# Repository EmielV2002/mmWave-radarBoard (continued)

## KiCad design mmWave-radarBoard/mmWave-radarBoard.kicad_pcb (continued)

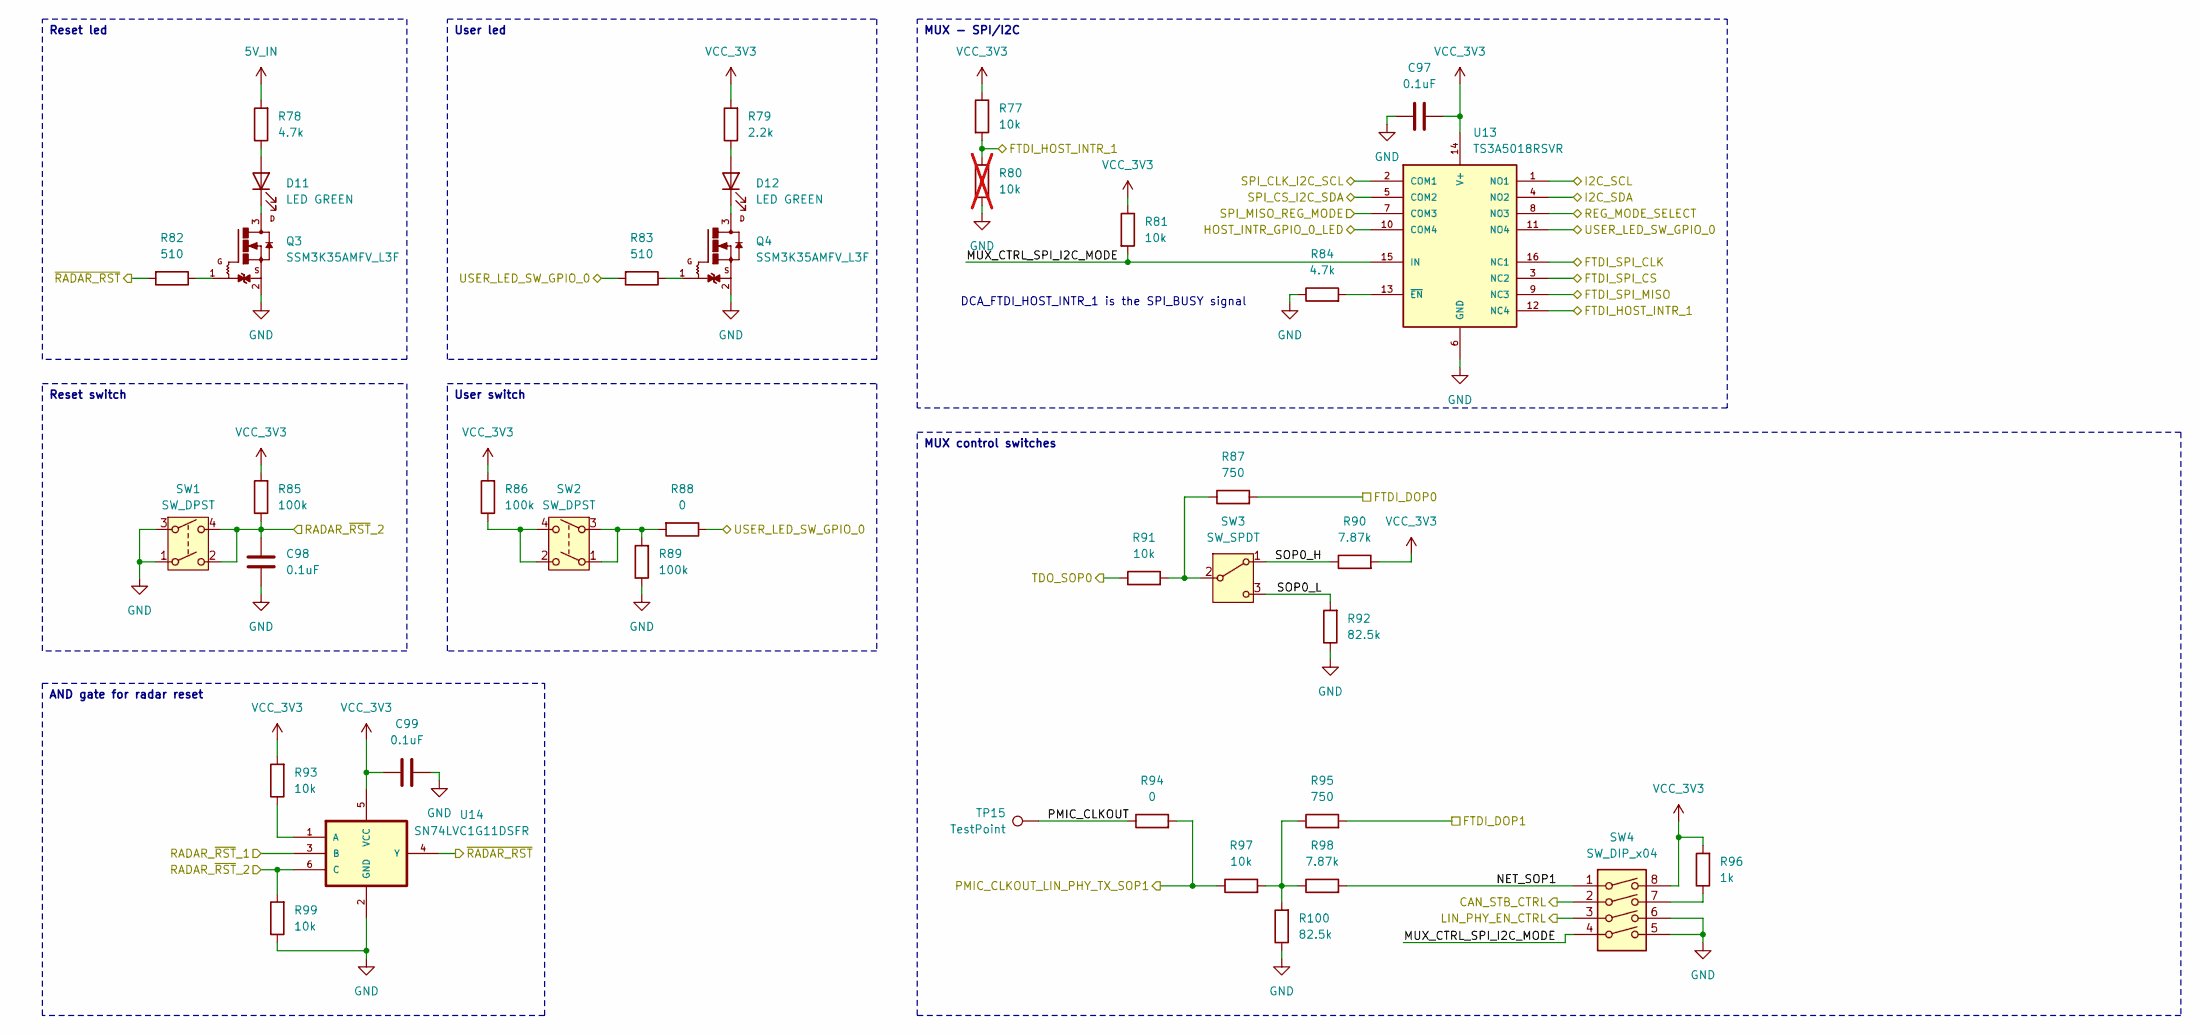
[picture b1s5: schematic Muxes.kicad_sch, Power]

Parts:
C97, C99: 0.1uF; C_0402_1005Metric
C98: 0.1uF; C_0603_1608Metric
D11, D12: LED GREEN; LED_0603_1608Metric
Q3, Q4: SSM3K35AMFV_L3F; VESM_TOS-M; MANUFACTURER_PART_NUMBER SSM3K35AMFV,L3F
R77, R81, R93, R99: 10k; R_0402_1005Metric
R78: 4.7k; R_0603_1608Metric
R79: 2.2k; R_0603_1608Metric
R80: 10k; R_0402_1005Metric; not fitted
R82, R83: 510; R_0402_1005Metric
R84: 4.7k; R_0402_1005Metric
R85, R86, R89: 100k; R_0603_1608Metric
R87, R95: 750; R_0603_1608Metric
R88, R94: 0; R_0603_1608Metric
R90, R98: 7.87k; R_0603_1608Metric
R91, R97: 10k; R_0603_1608Metric
R92, R100: 82.5k; R_0603_1608Metric
R96: 1k; R_0603_1608Metric
SW1, SW2: SW_DPST; SW_SPST_PTS810
SW3: SW_SPDT; Nidec_Copal_CAS-120A
SW4: SW_DIP_x04; SW_DIP_SPSTx04_Slide_6.7x11.72mm_W8.61mm_P2.54mm_LowProfile
TP15: TestPoint; TestPoint_Pad_D1.0mm
U13: TS3A5018RSVR; QFN40P260X180X55-16N; PARTREV 4220314/C 02/2020
U14: SN74LVC1G11DSFR; SON35P100X100X40-6N

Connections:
5V_IN: R78.2; also elsewhere on the board
/CAN_STB_CTRL: SW4.2; also elsewhere on the board
/FTDI_HOST_INT_1: R77.2, R80.1, U13.12 (NC4); also elsewhere on the board
/FTDI_SOP0: R87.2; also elsewhere on the board
/FTDI_SOP1: R95.2; also elsewhere on the board
/FTDI_SPI_CLK: U13.16 (NC1); also elsewhere on the board
/FTDI_SPI_CS: U13.3 (NC2); also elsewhere on the board
/FTDI_SPI_MISO: U13.9 (NC3); also elsewhere on the board
/HOST_INTR_GPIO_0_LED: U13.10 (COM4); also elsewhere on the board
/I2C_SCL: U13.1 (NO1); also elsewhere on the board
/I2C_SDA: U13.4 (NO2); also elsewhere on the board
/LIN_PHY_EN_CTRL: SW4.3; also elsewhere on the board
/Muxes/MUX_CTRL_SPI_I2C_MODE: R81.2, SW4.4, U13.15 (IN)
/Muxes/NET_SOP1: R98.2, SW4.1
/Muxes/PMIC_CLKOUT: R94.1, TP15.1
/Muxes/SOP0_H: R90.1, SW3.1 (A)
/Muxes/SOP0_L: R92.2, SW3.3 (C)
/PMIC_CLKOUT_LIN_PHY_TX_SOP1: R94.2, R97.1; also elsewhere on the board
/RADAR_~RST: R82.2, U14.4 (Y); also elsewhere on the board
/RADAR_~RST_1: U14.3 (B); also elsewhere on the board
/RADAR_~RST_2: C98.2, R85.1, R99.2, SW1.2, SW1.4, U14.6 (C); also elsewhere on the board
/REG_MODE_SELECT: U13.8 (NO3); also elsewhere on the board
/SPI_CLK_I2C_SCL: U13.2 (COM1); also elsewhere on the board
/SPI_CS_I2C_SDA: U13.5 (COM2); also elsewhere on the board
/SPI_MISO_REG_MODE: U13.7 (COM3); also elsewhere on the board
/TDO_SOP0: R91.1; also elsewhere on the board
/USER_LED_SW_GPIO_0: R83.2, R88.1, U13.11 (NO4); also elsewhere on the board
GND: C97.1, C98.1, C99.2, Q3.2, Q4.2, R80.2, R84.1, R89.1, R92.1, R99.1, R100.1, SW1.1, SW1.3, SW4.5, SW4.6, U13.6 (GND), U14.2 (GND); also elsewhere on the board
unnamed: D11.2 (A), R78.1
unnamed: D11.1 (K), Q3.3
unnamed: D12.2 (A), R79.1
unnamed: D12.1 (K), Q4.3
unnamed: Q3.1, R82.1
unnamed: Q4.1, R83.1
unnamed: R86.1, SW2.2, SW2.4
unnamed: R88.2, R89.2, SW2.1, SW2.3
unnamed: R96.1, SW4.7
unnamed: R95.1, R97.2, R98.1, R100.2
unnamed: R87.1, R91.2, SW3.2 (B)
unnamed: R84.2, U13.13 (~EN)
unnamed: R93.1, U14.1 (A)
VCC_3V3: C97.2, C99.1, R77.1, R79.2, R81.1, R85.2, R86.2, R90.2, R93.2, R96.2, SW4.8, U13.14 (V+), U14.5 (VCC); also elsewhere on the board

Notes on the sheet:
DCA_FTDI_HOST_INTR_1 is the SPI_BUSY signal
AND gate for radar reset
Reset led
MUX - SPI/I2C
Reset switch
User led
MUX control switches
User switch

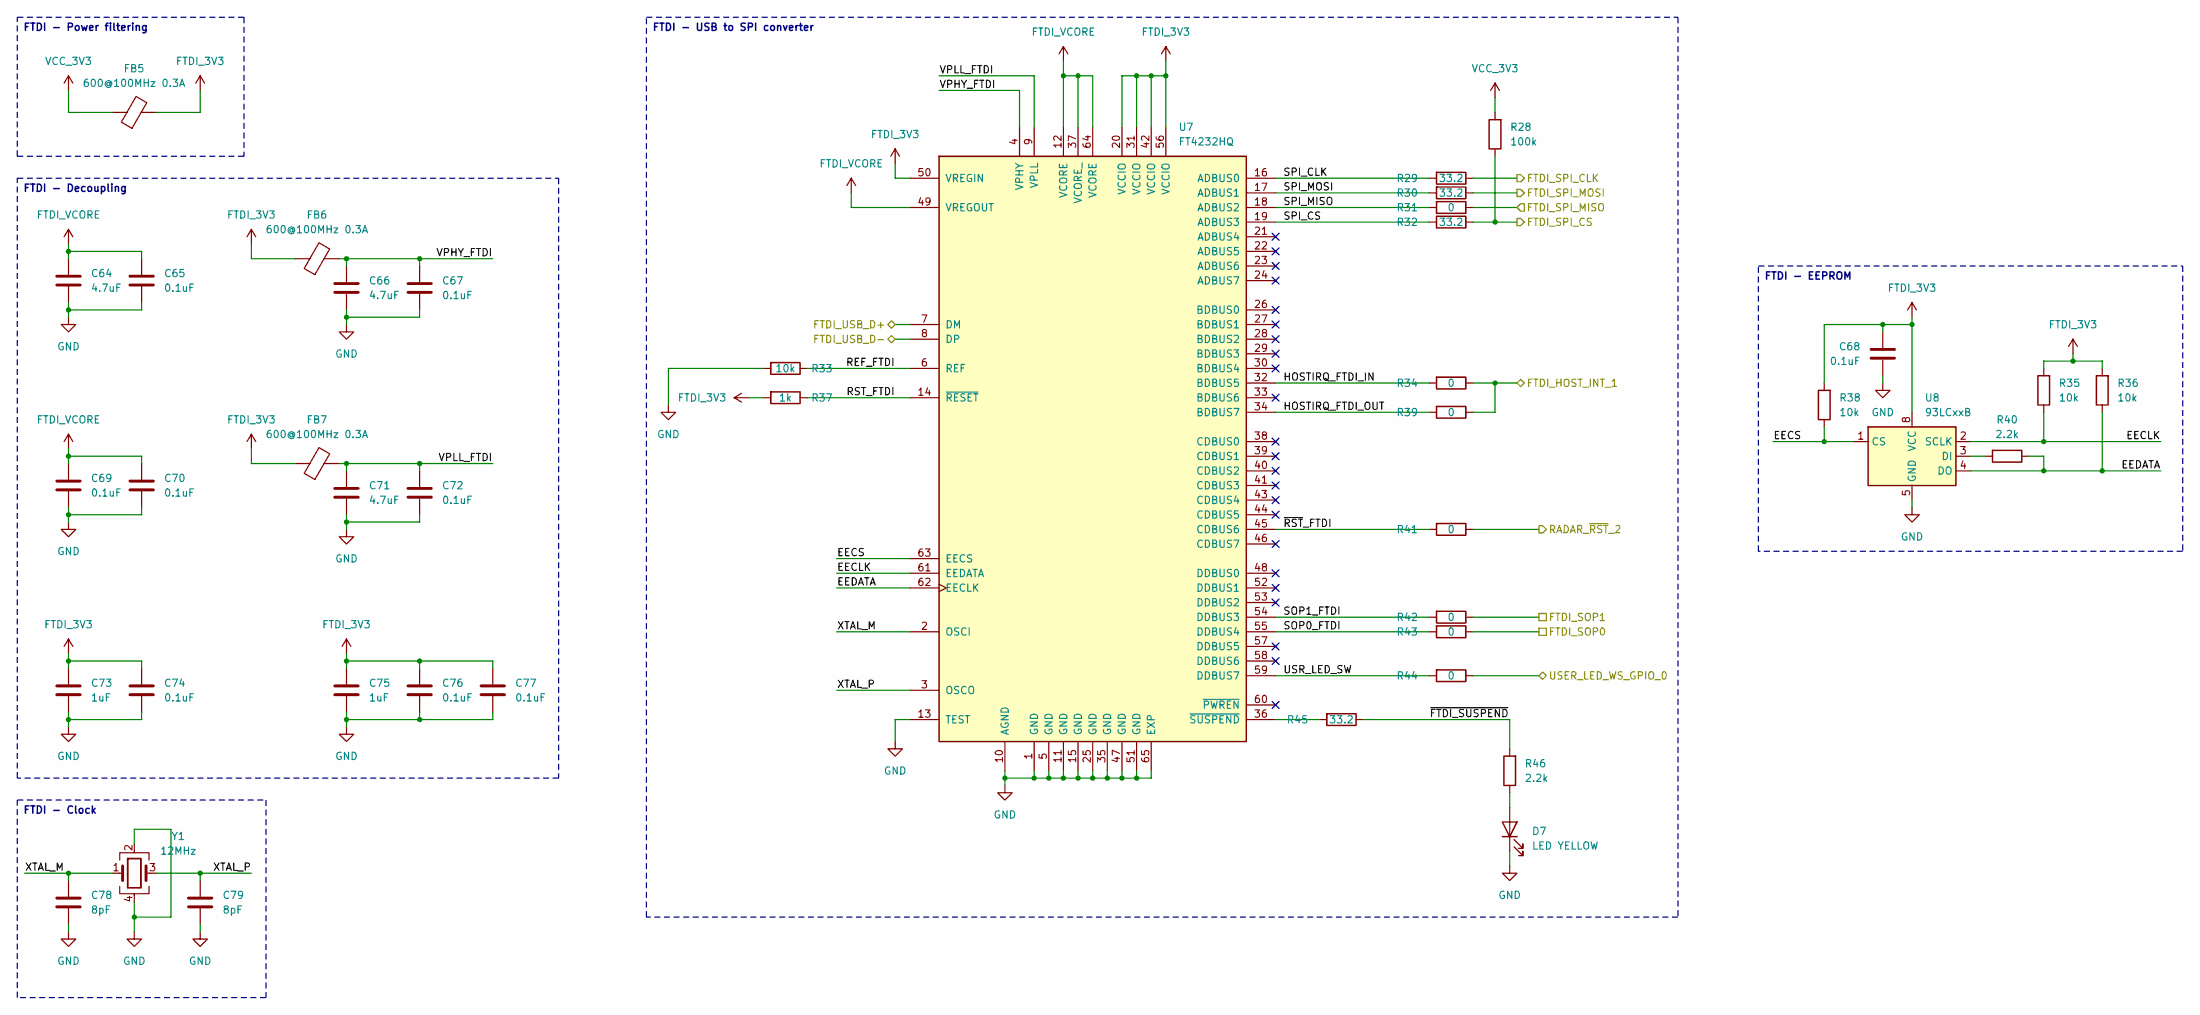
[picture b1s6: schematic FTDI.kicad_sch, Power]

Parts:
C64, C66, C71: 4.7uF; C_0402_1005Metric
C65, C67, C69, C70, C72, C74, C76, C77: 0.1uF; C_0402_1005Metric
C68: 0.1uF; C_0603_1608Metric
C73, C75: 1uF; C_0402_1005Metric
C78, C79: 8pF; C_0402_1005Metric
D7: LED YELLOW; LED_0603_1608Metric
FB5, FB6, FB7: 600@100MHz 0.3A; L_0603_1608Metric
R28: 100k; R_0402_1005Metric
R29, R30, R32, R45: 33.2; R_0402_1005Metric
R31, R34, R39, R41, R42, R43, R44: 0; R_0402_1005Metric
R33, R35, R36, R38: 10k; R_0402_1005Metric
R37: 1k; R_0402_1005Metric
R40: 2.2k; R_0402_1005Metric
R46: 2.2k; R_0603_1608Metric
U7: FT4232HQ; QFN50P900X900X105-65N; PARTREV 2.5
U8: 93LCxxB; SOIC-8_3.9x4.9mm_P1.27mm
Y1: 12MHz; Crystal_SMD_2016-4Pin_2.0x1.6mm

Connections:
/FTDI/EECLK: R35.1, U7.61 (EEDATA), U8.2 (SCLK)
/FTDI/EECS: R38.1, U7.63 (EECS), U8.1 (CS)
/FTDI/EEDATA: R36.1, R40.1, U7.62 (EECLK), U8.4 (DO)
/FTDI/HOSTIRQ_FTDI_IN: R34.2, U7.32 (BDBUS5)
/FTDI/HOSTIRQ_FTDI_OUT: R39.2, U7.34 (BDBUS7)
/FTDI/REF_FTDI: R33.1, U7.6 (REF)
/FTDI/RST_FTDI: R37.1, U7.14 (~RESET)
/FTDI/SOP0_FTDI: R43.2, U7.55 (DDBUS4)
/FTDI/SOP1_FTDI: R42.2, U7.54 (DDBUS3)
/FTDI/SPI_CLK: R29.2, U7.16 (ADBUS0)
/FTDI/SPI_CS: R32.2, U7.19 (ADBUS3)
/FTDI/SPI_MISO: R31.2, U7.18 (ADBUS2)
/FTDI/SPI_MOSI: R30.2, U7.17 (ADBUS1)
/FTDI/USR_LED_SW: R44.2, U7.59 (DDBUS7)
/FTDI/VPHY_FTDI: C66.1, C67.1, FB6.2, U7.4 (VPHY)
/FTDI/VPLL_FTDI: C71.1, C72.1, FB7.2, U7.9 (VPLL)
/FTDI/XTAL_M: C78.1, U7.2 (OSCI), Y1.1
/FTDI/XTAL_P: C79.1, U7.3 (OSCO), Y1.3
/FTDI/~FTDI_SUSPEND: R45.1, R46.2
/FTDI/~RST_FTDI: R41.2, U7.45 (CDBUS6)
/FTDI_HOST_INT_1: R34.1, R39.1; also elsewhere on the board
/FTDI_SOP0: R43.1; also elsewhere on the board
/FTDI_SOP1: R42.1; also elsewhere on the board
/FTDI_SPI_CLK: R29.1; also elsewhere on the board
/FTDI_SPI_CS: R28.1, R32.1; also elsewhere on the board
/FTDI_SPI_MISO: R30.1; also elsewhere on the board
/FTDI_SPI_MOSI: R31.1; also elsewhere on the board
/RADAR_~RST_2: R41.1; also elsewhere on the board
/USB_D+: U7.7 (DM); also elsewhere on the board
/USB_D-: U7.8 (DP); also elsewhere on the board
/USER_LED_SW_GPIO_0: R44.1; also elsewhere on the board
FTDI_3V3: C68.1, C73.1, C74.1, C75.1, C76.1, C77.1, FB5.2, FB6.1, FB7.1, R35.2, R36.2, R37.2, R38.2, U7.20 (VCCIO), U7.31 (VCCIO), U7.42 (VCCIO), U7.50 (VREGIN), U7.56 (VCCIO), U8.8 (VCC)
FTDI_VCORE: C64.1, C65.1, C69.1, C70.1, U7.12 (VCORE), U7.37 (VCORE_), U7.49 (VREGOUT), U7.64 (VCORE)
GND: C64.2, C65.2, C66.2, C67.2, C68.2, C69.2, C70.2, C71.2, C72.2, C73.2, C74.2, C75.2, C76.2, C77.2, C78.2, C79.2, D7.1 (K), R33.2, U7.1 (GND), U7.5 (GND), U7.10 (AGND), U7.11 (GND), U7.13 (TEST), U7.15 (GND), U7.25 (GND), U7.35 (GND), U7.47 (GND), U7.51 (GND), U7.65 (EXP), U8.5 (GND), Y1.2, Y1.4; also elsewhere on the board
unnamed: D7.2 (A), R46.1
unnamed: R45.2, U7.36 (~SUSPEND)
unnamed: R40.2, U8.3 (DI)
VCC_3V3: FB5.1, R28.2; also elsewhere on the board

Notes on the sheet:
FTDI - Decoupling
FTDI - Clock
FTDI - USB to SPI converter
FTDI - EEPROM
FTDI - Power filtering

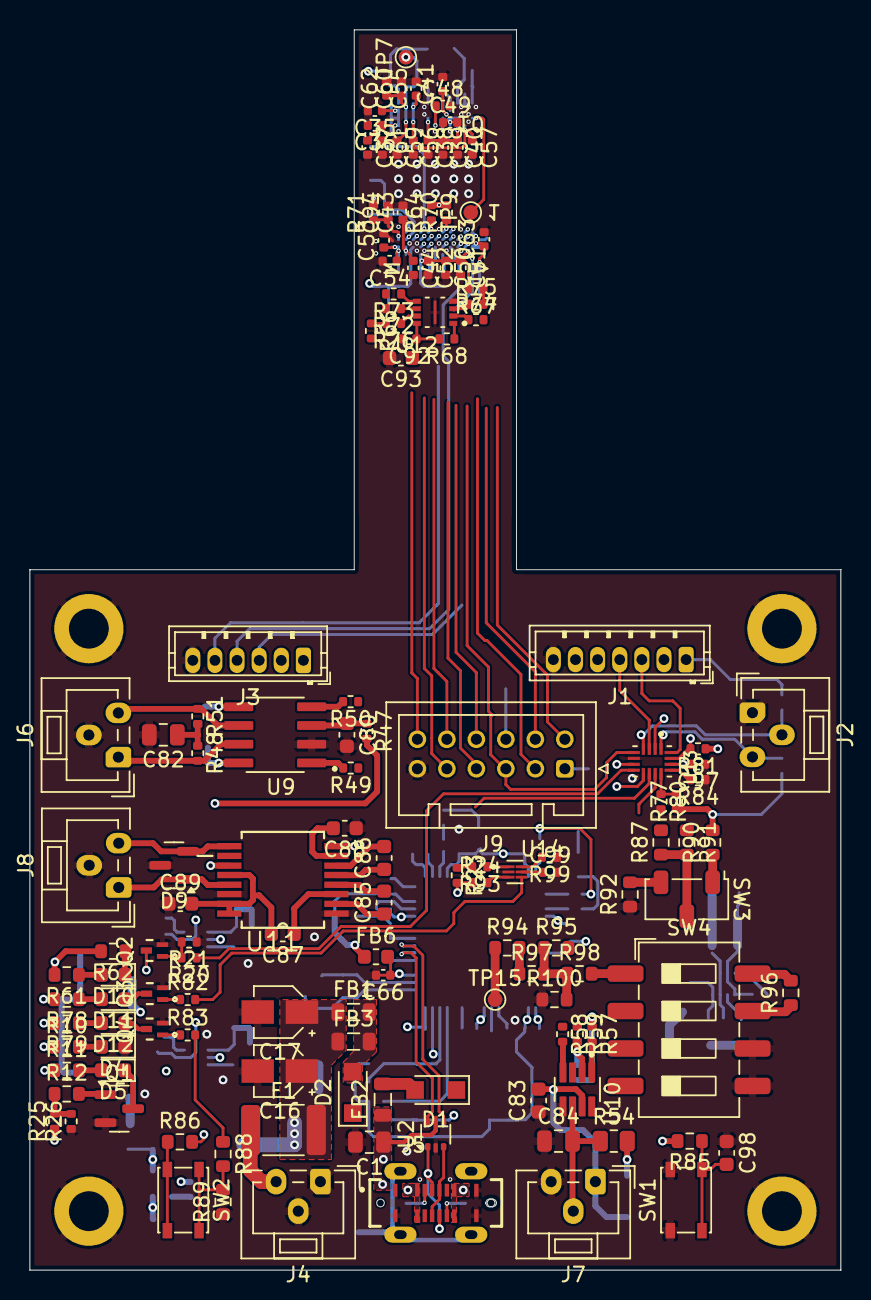
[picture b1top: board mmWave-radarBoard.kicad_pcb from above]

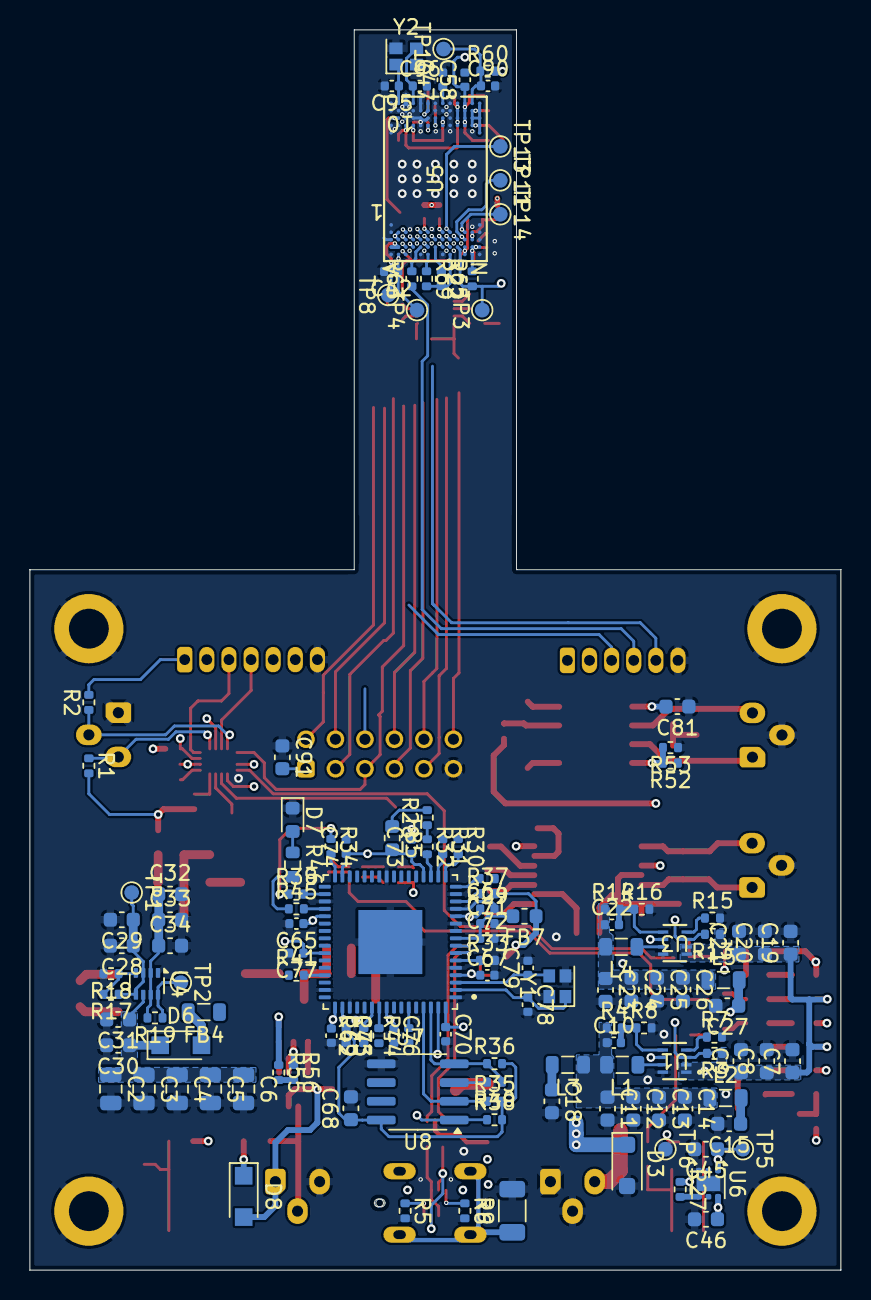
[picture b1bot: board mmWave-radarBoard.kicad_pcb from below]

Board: 6 copper layers, 55.0 x 84.1 mm, 275 parts (133 on the bottom side), 164 nets.

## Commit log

2025-04-12 Initial setup
2025-04-13 Started working on the schematic
2025-04-14 Updated schematic
2025-04-15 Updated schematic of the radar module
2025-04-16 Removed unnecessary bits
2025-04-19 Finished schematic
2025-04-19 Updated radar PCB and schematic
2025-04-20 Updated schematic and PCB
2025-04-21 Create design
2025-04-23 Updated PCB and schematic
2025-04-29 Updated PCB
2025-05-05 Updated schematic and layout PCB
2025-05-06 Started routing
